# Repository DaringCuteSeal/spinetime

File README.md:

# Spinetime

[Magazine PDF](showcase/zine.pdf)

[Watch the short demo here!](https://www.youtube.com/shorts/rvpcNDkeEeY)

---

Spinetime is a ring binder-integrated _linear clock [^1]_ designed to help
students and neurodivergent individuals manage time and tasks more effectively.
Users of Spinetime can visualize the passage of the day at a glance, providing
aid especially for those who struggle with time blindness.

## Why?

It is surprising to me that people have manufactured papers with time table
template, but not invent something as simple as a pointer that tells you how
far you have gone through your table. I suspect that this is because most
people do not experience time blindness, and having some kind of pointer of the
table isn't really all that useful. This is simply not the case for those with
time blindness: **time doesn't really mean anything if presented in the wrong
way.** I hope that the proof of concept that came with Spinetime may help
present time meaningfully for those who struggle with time blindness like me.

## Background

As someone who suffers from time blindness on a daily basis, I find managing my
time extremely challenging. It's been intensely hard to picture how I'll spend
my time for a particular day. Having shuffled between multiple time management
methods, I constantly find myself at home when I plan my day out on my physical
journal. I simply love the tactile feel of using a physical tool to plan out my
day.

However, being the visual-oriented person I am, lacking any visual cue of
"where" in the time dimension I am at any given day has been a major
deal-breaker that has kept me from using physical tools for journalling. Of
course, journalling papers with pre-made time tables exist, but they don't tell
me what time it really is right now in any tangible manner relating to the table
itself—what a bummer.

I've been using [ChronoCat](https://chronocat.app/) (not affiliated) to manage
my time lately, and it's been a perfect digital tool—minimalistic,
very visual, and easy to use. It provides the user with a
time table alongside a visual cue of where they are within the day.
However, like I said before, I crave the tactile feel of physical
note-taking. It'd also be great if I can plan my day without the distraction
that comes with using a full-fledged mobile phone or computer.
Plus, being able to plan my day at school would be a great[^2]. I always
dream that one day, I won't forget several of my appointments again.

I looked at my own journalling book again, and thought: _you know, I
think that ChronoCat's approach doesn't have to be in the form of a
digital app._ And so, I came up with SpineTime.

## How to Use

**Daily use**: simply strap Spinetime to your ring binder by opening the spine and inserting
the linear clock component and start annotating your day. This repository hosts
the A6 binder-compatible
version.

**How to charge the battery**: charge with a type-C cable. 5V, obviously. The controller implements load sharing so you'll be powering the circuit directly with the given 5V when charged.

## How it Works
The LEDs of the bookmark are controlled by a separate controller unit. An ATtiny1616 MCU is used alongside a DS3231 RTC.

## Specs
- Power usage: about 20-25 mA when bookmark is on (3.7V * 25mA = 92.5 mW). Depends on LED color. 7 mA when bookmark is switched off (3.7V * 7mA = 25.9 mW).
- Use duration: about 1d 16h (1000 mAh ÷ 25 mA). Probably a bit lower since we won't (and can't) use the full capacity of the battery.

## Build Instruction
You will need:
1. A soldering iron
2. Solder
3. Everything from [BOM](#BOM)
4. A USB-to-TTL adapter such as a CH340 breakout module
5. Wire crimper
6. Wire stripper
7. Scissors
8. USB-C cable
9. 3 jumper wires (female-to-female)

Steps:
1. Print the [PCBs](#Project-Design-Showcase). Customize if needed. Note that the gerbers aren't included, so you'd have to generate them first from KiCad.
2. Solder components listed on the [BOM](#BOM) according to the PCB file.
3. 3D print the casing components.
4. Use whatever set of cables you have (can be thin) and solder the bookmark's VIN, GND, and DAT through-holes to the cables. Crimp the end into the 3-pin JST housing. Make sure the orientation is aligned correctly with the controller (as JST connectors cannot be plugged in both orientations).
5. Put together everything into the casing: the battery, the controller PCB, and the anti-slip rubbers (might need to be cut to the correct size first, fitting the casing's square indents).
6. If your battery hasn't been crimped yet, crimp the cables to the 2-pin JST. Then plug the battery connector to the controller.
7. Build the [firmware](#firmware). Customize as you wish. You'll need [PlatformIO](https://platformio.org/).
8. FLash the firmware. Initially, set `SET_TIME` to `true` in the `cfg.h` file first to set time, then flash again with `SET_TIME` set to `false`. You will need a USB-to-TTL adapter. Connect the TX pin of the adapter to the TX pin of SpineTime's controller PCB and the RX pin of the adapter to RX. Note that the PCB doesn't have labels for that.. just check the kicad file to know which is which :P. Then, connect the adapter's ground accordingly.
9. You should be done! There's no screw assembly required—everything uses compliant mechanism.

Gotchas:
1. If you can't flash the ATtiny1616, try changing to another device. Initially I couldn't flash my ATtiny and as it turns out, my laptop has a bad USB controller.
2. Some sources online say that SK6812 LEDs are difficult to solder and require lower temp but I found that with hand-soldering, even up to ~350°C is fine. (just don't roast the LEDs for 1 minute straight I guess)

## Spelling
Spinetime, SpineTime, spinetime are all valid. No spineTime or spine_time or anything else.
## Project Design Showcase

### IRL Build

Note: I built it with LEDs too big so I didn't put on the casing lid.

### PCBs

The actual bookmark ([project files](kicad/bookmark), [.step file](kicad/bookmark/bookmark.step)):

The controller unit ([project files](kicad/controller), [.step file](kicad/controller/controller.step)):

Schematics:

- [Schematic of controller unit](showcase/controller.pdf)
- [Schematic of bookmark unit](showcase/bookmark.pdf)

### 3D Models

The model files can be found under [freecad/](freecad/).

Casing:

Support clip (so your book cover won't wobble when being written on):

### Firmware
The firmware files for SpineTime, `spinetime-fw`, can be [found in the firmware directory](./firmware).

## BOM
[BOM/bill of materials for this project can be found here](bom/bom.csv).

## Credits

Thanks to [Hack Club](https://hackclub.com/) for supporting! Initially made for [Hack Club Blueprint](https://blueprint.hackclub.com), but later got transferred to [Hack Club Fallout](https://fallout.hackclub.com/).

**Awesome software used:**
- [KiCad](https://www.kicad.org/) (as EDA)
- [Blender](https://www.blender.org/) (for designing mockup)
- [FreeCAD](https://www.freecad.org/) (as CAD)
- [NeoVim](https://neovim.io/) (as IDE)
- [VSCode](https://code.visualstudio.com/) (as IDE)
- [PlatformIO](https://platformio.org/) (as embedded programming platform)
- [Kitty](https://sw.kovidgoyal.net/kitty/) (as terminal)
- [Git](https://git-scm.com/) (as SVC)
- [Artix Linux!](https://artixlinux.org)

**Awesome services used:**
- [Github](.) (hosting project files)

**I used several 3D models for my PCB 3D model:**
- https://grabcad.com/library/usb-type-c-smd-6pin-1
- https://grabcad.com/library/2-pins-jst-1
- https://grabcad.com/library/3-pins-jst-1

**References (unfortunately not all, just the very notable ones):**
- megaTinyCore, awesome core + documentations for my ATTiny: https://github.com/SpenceKonde/megaTinyCore)
- Datasheet of all components I used. I'm not sure if I wanna include all of the links back because I didn't keep track of them, but feel free to ask for the documents I have locally directly to maybe figure out the source.
- NeoPixel guide: https://learn.adafruit.com/adafruit-neopixel-uberguide/logic-level
- Another NeoPixel guide: https://www.digikey.com/en/maker/projects/adafruit-neopixel-berguide/970445a726c1438a9023c1e78c42e0bb
- How to flash ATtiny1616: https://michael-crum.com/attiny1616/
- Changing clock speed of ATtiny1616: https://www.avrfreaks.net/s/topic/a5C3l000000Ubn4EAC/t159058
- Technical problems with SK6812: https://forums.adafruit.com/viewtopic.php?t=188940
- Sk6812 is hard to solder?: https://www.makerfabs.com/blog/post/how-makerfabs-solve-the-oled-sticking-problem
- Order with moisture-sensitive devices recommendations: https://jlcpcb.com/help/article/moisture-sensitivity-level-msl-for-electronic-parts
- Load-sharing circuit: https://www.thanassis.space/loadsharing.html
- SMD resistor guide: https://www.allpcb.com/blog/pcb-assembly/smd-resistors-demystified-sizes-markings-and-practical-applications.html
- Should LED strip's end be connected to anything?: https://www.reddit.com/r/AskElectronics/comments/1bnx4vv/addressable_led_data_out_connect_to_ground_yn/
- TP4056 breakout reference: https://github.com/alltheworld/tp4056/issues/3
- Setting internal reference voltage for attiny1616: https://forum.arduino.cc/t/how-to-measure-supply-voltage-in-attiny/1244260

Huh, am I over-crediting? maybe..
## LLM Usage Disclosure
I used [ChatGPT](https://chatgpt.com) for sanity-checking my configurations (including my controller schematic, for instance it caught that I didn't pull the CC pins to ground).

[^1]: Analog clock that shows time in a linear format, instead of the usual
12-hour wrap-around style. This clock is often suggested for those with ADHD &
time blindness.

[^2]: My school does not allow the use of mobile phone/laptop during class and
recess.

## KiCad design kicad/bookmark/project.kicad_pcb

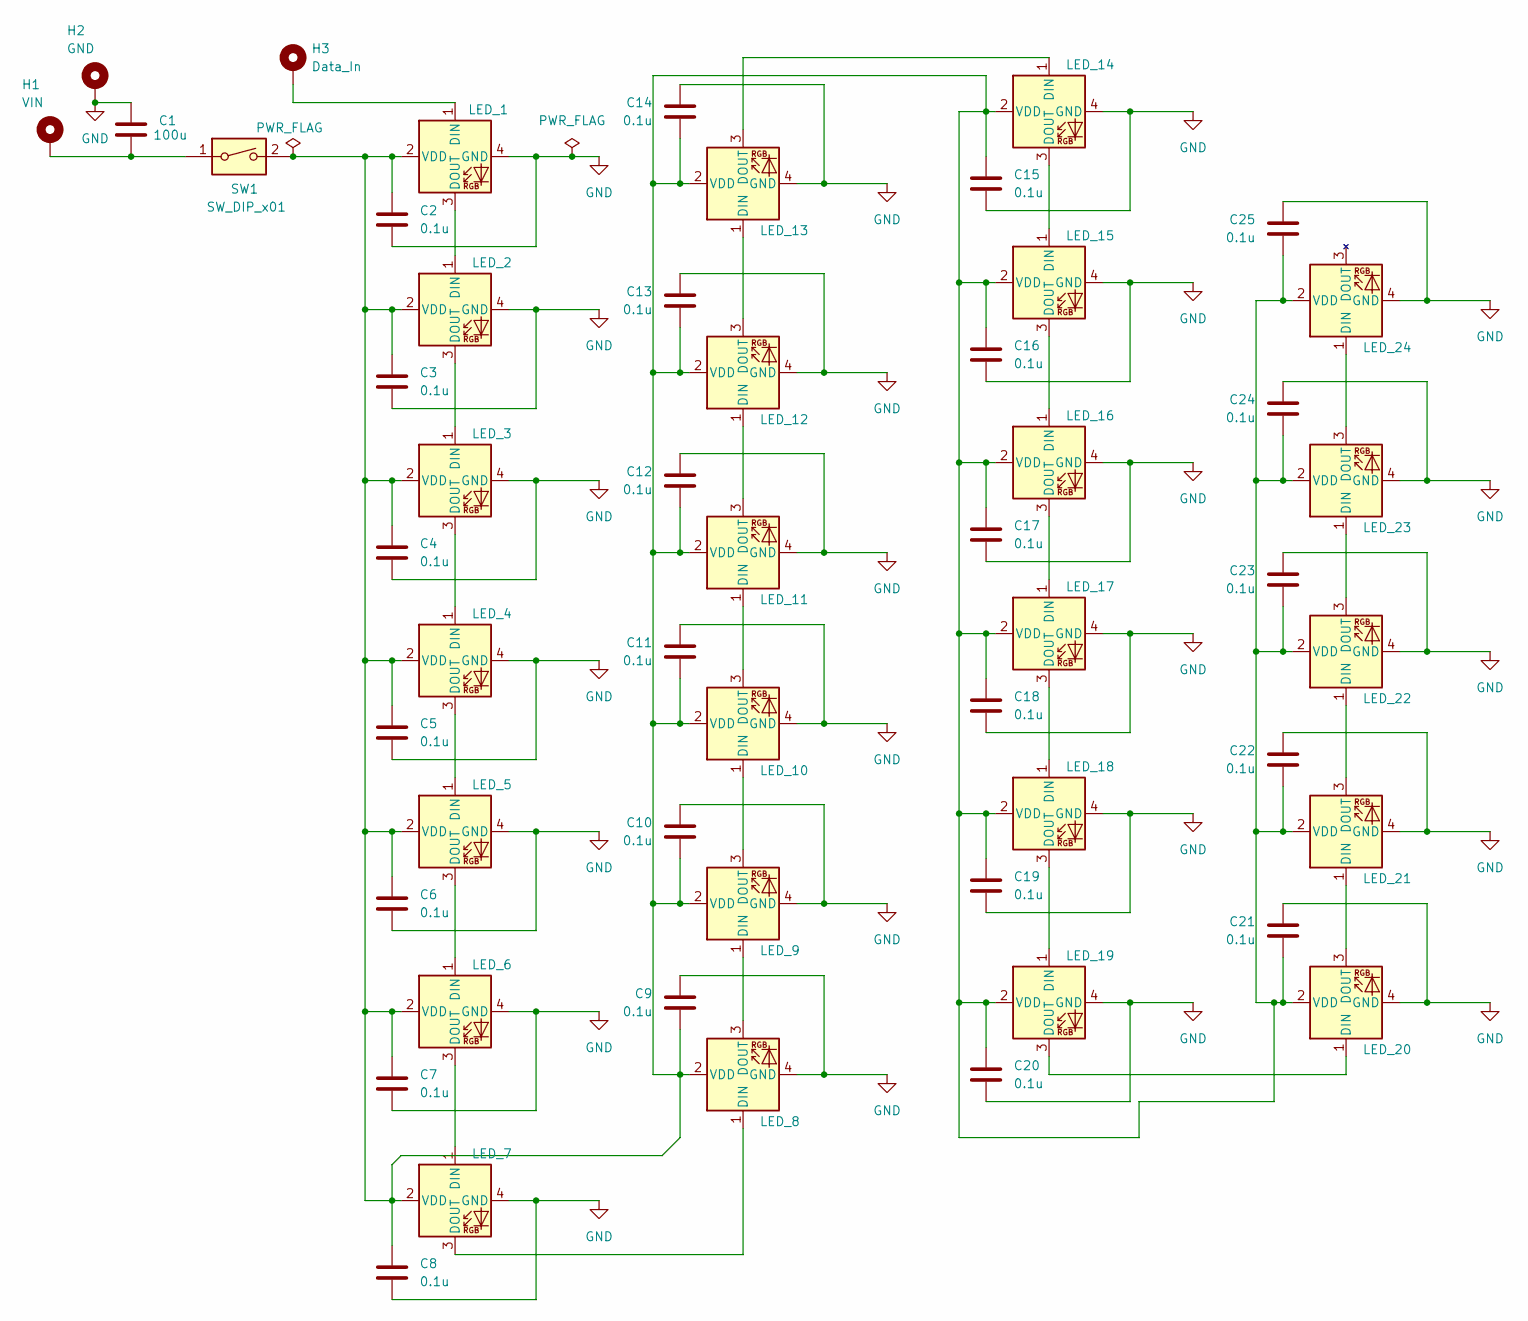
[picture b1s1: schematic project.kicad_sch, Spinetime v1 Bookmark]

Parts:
C1: 100u; C_1206_3216Metric
C2, C3, C4, C5, C6, C7, C8, C9, C10, C11, C12, C13, C14, C15, C16, C17, C18, C19, C20, C21, C22, C23, C24, C25: 0.1u; C_0402_1005Metric
D1: LED_1; LED-SMD_4P-L4.0-W1.6-L
D2: LED_2; LED-SMD_4P-L4.0-W1.6-L
D3: LED_3; LED-SMD_4P-L4.0-W1.6-L
D4: LED_4; LED-SMD_4P-L4.0-W1.6-L
D5: LED_5; LED-SMD_4P-L4.0-W1.6-L
D6: LED_6; LED-SMD_4P-L4.0-W1.6-L
D7: LED_7; LED-SMD_4P-L4.0-W1.6-L
D8: LED_8; LED-SMD_4P-L4.0-W1.6-L
D9: LED_9; LED-SMD_4P-L4.0-W1.6-L
D10: LED_10; LED-SMD_4P-L4.0-W1.6-L
D11: LED_11; LED-SMD_4P-L4.0-W1.6-L
D12: LED_12; LED-SMD_4P-L4.0-W1.6-L
D13: LED_13; LED-SMD_4P-L4.0-W1.6-L
D14: LED_14; LED-SMD_4P-L4.0-W1.6-L
D15: LED_15; LED-SMD_4P-L4.0-W1.6-L
D16: LED_16; LED-SMD_4P-L4.0-W1.6-L
D17: LED_17; LED-SMD_4P-L4.0-W1.6-L
D18: LED_18; LED-SMD_4P-L4.0-W1.6-L
D19: LED_19; LED-SMD_4P-L4.0-W1.6-L
D20: LED_20; LED-SMD_4P-L4.0-W1.6-L
D21: LED_21; LED-SMD_4P-L4.0-W1.6-L
D22: LED_22; LED-SMD_4P-L4.0-W1.6-L
D23: LED_23; LED-SMD_4P-L4.0-W1.6-L
D24: LED_24; LED-SMD_4P-L4.0-W1.6-L
H1: VIN; THT_hole_2mm
H2: GND; THT_hole_2mm
H3: Data_In; THT_hole_2mm
SW1: SW_DIP_x01; SW-SMD_CHS-01B

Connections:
GND: C1.1, C2.2, C3.2, C4.2, C5.2, C6.2, C7.2, C8.2, C9.2, C10.2, C11.2, C12.2, C13.2, C14.2, C15.2, C16.2, C17.2, C18.2, C19.2, C20.2, C21.2, C22.2, C23.2, C24.2, C25.2, D1.4 (GND), D2.4 (GND), D3.4 (GND), D4.4 (GND), D5.4 (GND), D6.4 (GND), D7.4 (GND), D8.4 (GND), D9.4 (GND), D10.4 (GND), D11.4 (GND), D12.4 (GND), D13.4 (GND), D14.4 (GND), D15.4 (GND), D16.4 (GND), D17.4 (GND), D18.4 (GND), D19.4 (GND), D20.4 (GND), D21.4 (GND), D22.4 (GND), D23.4 (GND), D24.4 (GND), H2.1 (1_1)
unnamed: C1.2, H1.1 (1_1), SW1.1
unnamed: D1.1 (DIN), H3.1 (1_1)
unnamed: D1.3 (DOUT), D2.1 (DIN)
unnamed: C2.1, C3.1, C4.1, C5.1, C6.1, C7.1, C8.1, C9.1, C10.1, C11.1, C12.1, C13.1, C14.1, C15.1, C16.1, C17.1, C18.1, C19.1, C20.1, C21.1, C22.1, C23.1, C24.1, C25.1, D1.2 (VDD), D2.2 (VDD), D3.2 (VDD), D4.2 (VDD), D5.2 (VDD), D6.2 (VDD), D7.2 (VDD), D8.2 (VDD), D9.2 (VDD), D10.2 (VDD), D11.2 (VDD), D12.2 (VDD), D13.2 (VDD), D14.2 (VDD), D15.2 (VDD), D16.2 (VDD), D17.2 (VDD), D18.2 (VDD), D19.2 (VDD), D20.2 (VDD), D21.2 (VDD), D22.2 (VDD), D23.2 (VDD), D24.2 (VDD), SW1.2
unnamed: D2.3 (DOUT), D3.1 (DIN)
unnamed: D3.3 (DOUT), D4.1 (DIN)
unnamed: D4.3 (DOUT), D5.1 (DIN)
unnamed: D5.3 (DOUT), D6.1 (DIN)
unnamed: D6.3 (DOUT), D7.1 (DIN)
unnamed: D7.3 (DOUT), D8.1 (DIN)
unnamed: D8.3 (DOUT), D9.1 (DIN)
unnamed: D9.3 (DOUT), D10.1 (DIN)
unnamed: D10.3 (DOUT), D11.1 (DIN)
unnamed: D11.3 (DOUT), D12.1 (DIN)
unnamed: D12.3 (DOUT), D13.1 (DIN)
unnamed: D13.3 (DOUT), D14.1 (DIN)
unnamed: D14.3 (DOUT), D15.1 (DIN)
unnamed: D15.3 (DOUT), D16.1 (DIN)
unnamed: D16.3 (DOUT), D17.1 (DIN)
unnamed: D17.3 (DOUT), D18.1 (DIN)
unnamed: D18.3 (DOUT), D19.1 (DIN)
unnamed: D19.3 (DOUT), D20.1 (DIN)
unnamed: D20.3 (DOUT), D21.1 (DIN)
unnamed: D21.3 (DOUT), D22.1 (DIN)
unnamed: D22.3 (DOUT), D23.1 (DIN)
unnamed: D23.3 (DOUT), D24.1 (DIN)

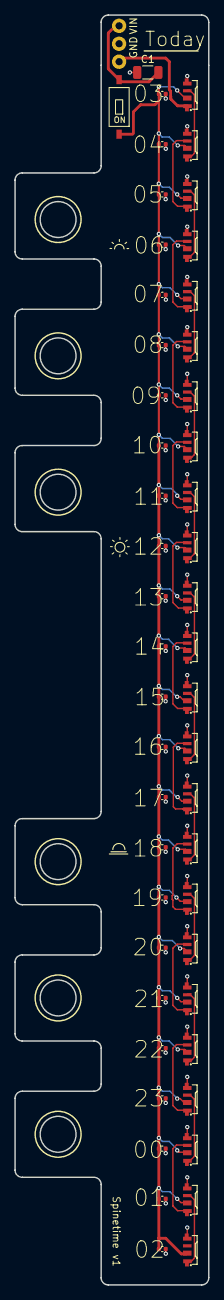
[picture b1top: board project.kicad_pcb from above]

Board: 2 copper layers, 27.0 x 177.0 mm, 53 parts (0 on the bottom side), 27 nets.

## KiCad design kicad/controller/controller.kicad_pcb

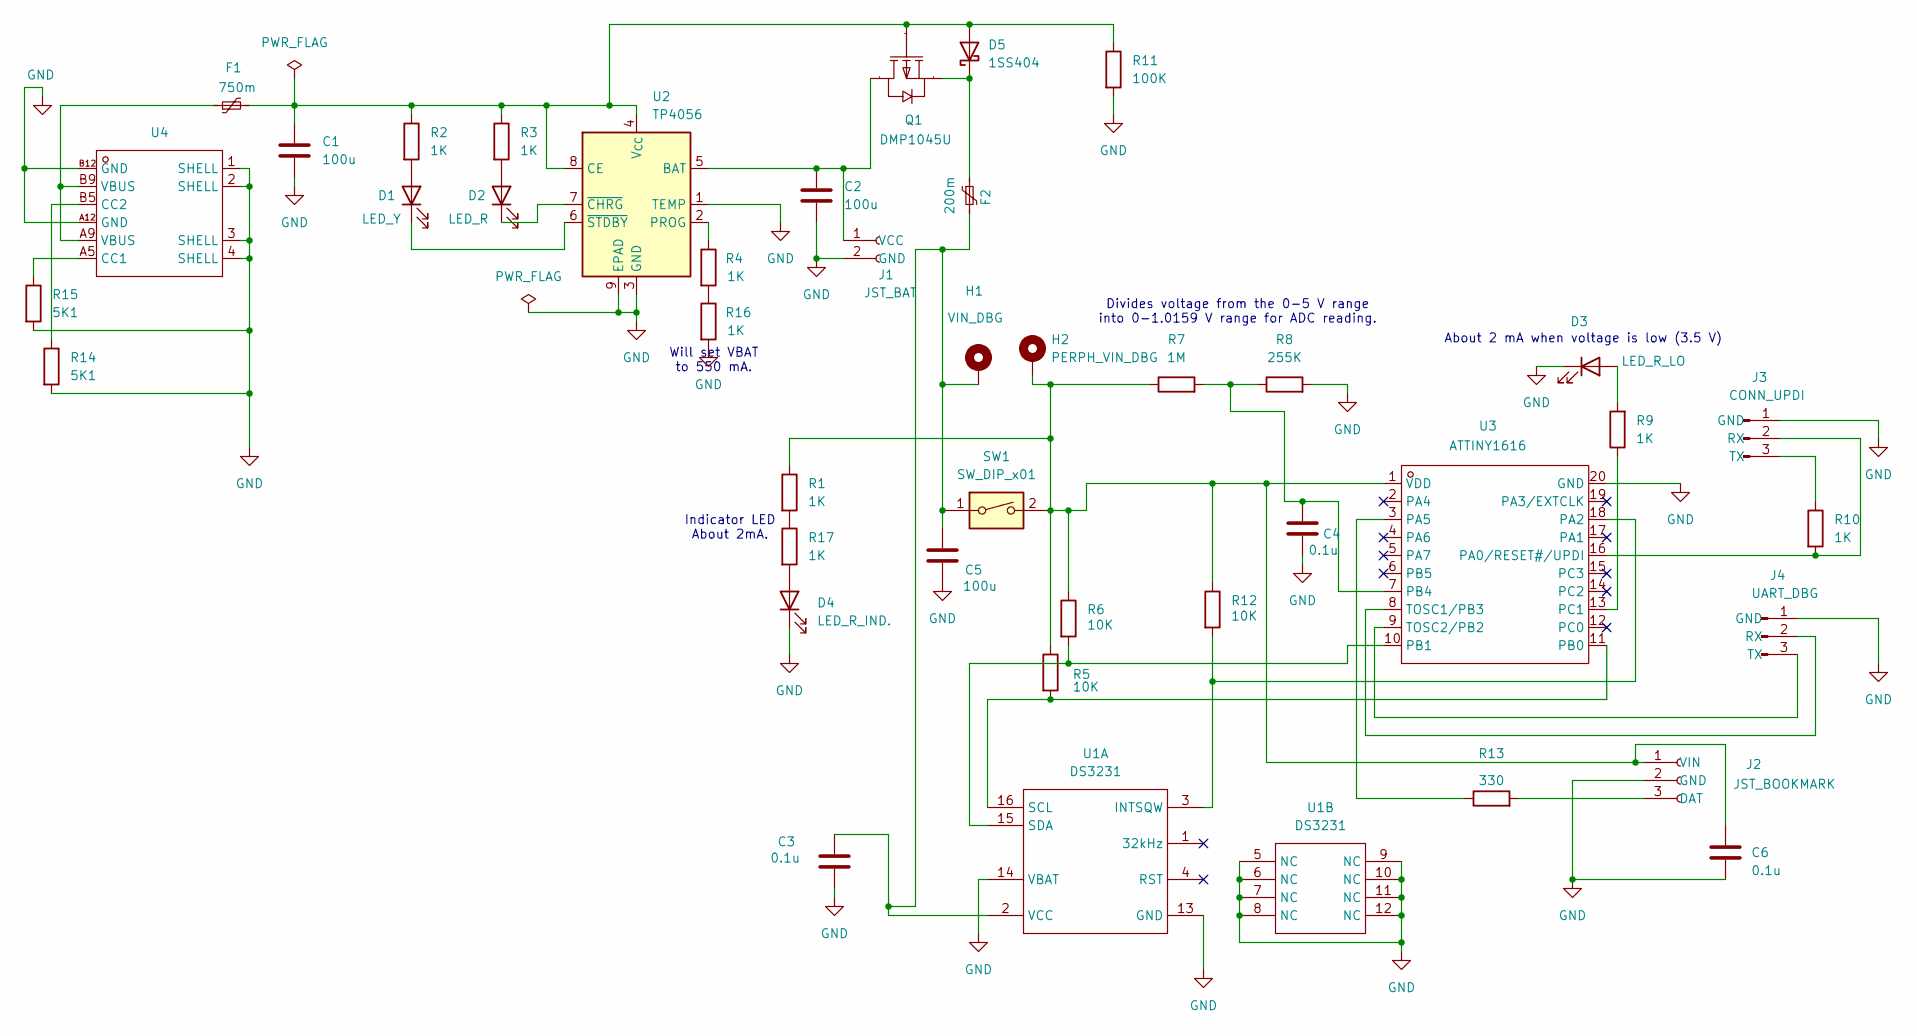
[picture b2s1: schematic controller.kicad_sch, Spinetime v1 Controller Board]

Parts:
C1, C2, C5: 100u; C_1206_3216Metric
C3, C4, C6: 0.1u; C_0402_1005Metric
D1: LED_Y; LED_D2.0mm_W4.8mm_H2.5mm_FlatTop
D2: LED_R; LED_D2.0mm_W4.8mm_H2.5mm_FlatTop
D3: LED_R_LO; LED_D2.0mm_W4.8mm_H2.5mm_FlatTop
D4: LED_R_IND.; LED_D2.0mm_W4.8mm_H2.5mm_FlatTop
D5: 1SS404; D_SOD-323
F1: 750m; Fuse_1812_4532Metric
F2: 200m; Fuse_1812_4532Metric
H1: VIN_DBG; SolderWirePad_1x01_SMD_1x2mm
H2: PERPH_VIN_DBG; SolderWirePad_1x01_SMD_1x2mm
J1: JST_BAT; JST_1x2_2.54mm-horizontal_1
J2: JST_BOOKMARK; JST_1x3_2.54mm-horizontal
J3: CONN_UPDI; PinHeader_1x03_P2.54mm_Vertical
J4: UART_DBG; PinHeader_1x03_P2.54mm_Vertical
Q1: DMP1045U; SOT-23-3_L2.9-W1.5-P1.90-LS2.6-BR; Manufacturer Part DMP1045U-HXY; LCSC Part Name 1个P沟道 耐压:20V 电流:5A
R1, R2, R3, R4, R9, R10, R16, R17: 1K; R_0603_1608Metric
R5, R6, R12: 10K; R_0603_1608Metric
R7: 1M; R_0603_1608Metric
R8: 255K; R_0603_1608Metric
R11: 100K; R_0603_1608Metric
R13: 330; R_0603_1608Metric
R14, R15: 5K1; R_0603_1608Metric
SW1: SW_DIP_x01; SW-SMD_CHS-01B
U1: DS3231; SOIC-16_L10.3-W7.5-P1.27-LS10.3-BL; Manufacturer Part DS3231SN#T&R; LCSC Part Name 超高精度、I²C接口、集成RTC/TCXO/晶体
U2: TP4056; SOIC-8-1EP_3.9x4.9mm_P1.27mm_EP2.41x3.3mm_ThermalVias
U3: ATTINY1616; SOIC-20_L12.8-W7.5-P1.27-LS10.3-BL; Manufacturer Part ATTINY1616-SNR; LCSC Part Name tinyAVR 1系列微控制器
U4: USB-C-SMD_USB-TYPE-C-006; Manufacturer Part USB-TYPE-C-006; LCSC Part Name Type-C 母 卧贴

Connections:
GND: C1.2, C2.2, C3.2, C4.2, C5.2, C6.2, D3.1 (K), D4.1 (K), J1.2 (GND), J2.2 (GND), J3.1 (GND), J4.1 (GND), R8.2, R11.2, R14.2, R15.2, R16.2, U1.5 (NC), U1.6 (NC), U1.7 (NC), U1.8 (NC), U1.9 (NC), U1.10 (NC), U1.11 (NC), U1.12 (NC), U1.13 (GND), U1.14 (VBAT), U2.1 (TEMP), U2.3 (GND), U2.9 (EPAD), U3.20 (GND), U4.1 (SHELL), U4.2 (SHELL), U4.3 (SHELL), U4.4 (SHELL), U4.A12 (GND), U4.B12 (GND)
unnamed: D1.2 (A), R2.2
unnamed: D1.1 (K), U2.6 (~STDBY)
unnamed: D2.2 (A), R3.2
unnamed: D2.1 (K), U2.7 (~CHRG)
unnamed: D3.2 (A), R9.2
unnamed: D4.2 (A), R17.2
unnamed: C1.1, D5.2 (A), F1.2, Q1.1 (G), R2.1, R3.1, R11.1, U2.4 (V_{CC}), U2.8 (CE)
unnamed: D5.1 (K), F2.1, Q1.2 (S)
unnamed: F1.1, U4.A9 (VBUS), U4.B9 (VBUS)
unnamed: C2.1, J1.1 (VCC), Q1.3 (D), U2.5 (BAT)
unnamed: J2.3 (DAT), R13.2
unnamed: C6.1, H2.1 (1_1), J2.1 (VIN), R1.1, R5.1, R6.1, R7.1, R12.1, SW1.2, U3.1 (VDD)
unnamed: J3.2 (RX), R10.2, U3.16 (PA0/RESET#/UPDI)
unnamed: J3.3 (TX), R10.1
unnamed: J4.2 (RX), U3.8 (TOSC1/PB3)
unnamed: J4.3 (TX), U3.9 (TOSC2/PB2)
unnamed: R1.2, R17.1
unnamed: R4.2, R16.1
unnamed: R12.2, U1.3 (INTSQW), U3.18 (PA2)
unnamed: R5.2, U1.16 (SCL), U3.11 (PB0)
unnamed: R6.2, U1.15 (SDA), U3.10 (PB1)
unnamed: C3.1, C5.1, F2.2, H1.1 (1_1), SW1.1, U1.2 (VCC)
unnamed: R4.1, U2.2 (PROG)
unnamed: R13.1, U3.3 (PA5)
unnamed: C4.1, R7.2, R8.1, U3.7 (PB4)
unnamed: R9.1, U3.13 (PC1)
unnamed: R15.1, U4.A5 (CC1)
unnamed: R14.1, U4.B5 (CC2)

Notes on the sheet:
Indicator LED About 2mA.
Divides voltage from the 0-5 V range into 0-1.0159 V range for ADC reading.
Will set VBAT to 550 mA.
About 2 mA when voltage is low (3.5 V)

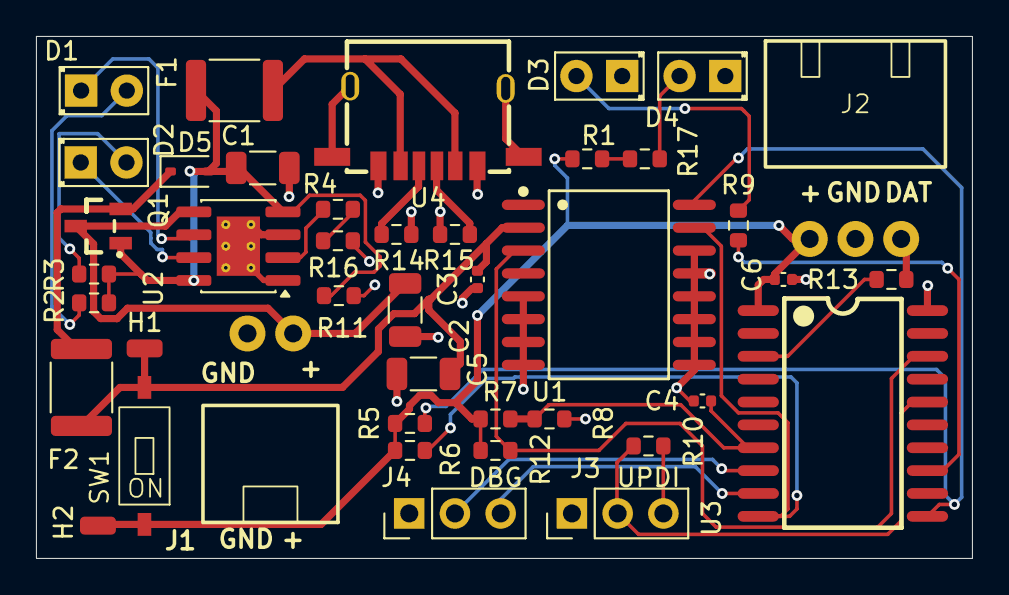
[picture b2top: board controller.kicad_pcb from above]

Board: 2 copper layers, 52.0 x 29.0 mm, 42 parts (0 on the bottom side), 29 nets.

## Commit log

2026-02-15 docs: add README file
2026-02-15 docs: improve README file formatting & grammar
2026-02-15 docs: remove use of pascalcase project name
2026-03-26 add project and model files
2026-03-28 fix: correct LED footprints
2026-03-28 fix: fix wrong UPDI & DBG pin label
2026-03-29 chore: rename model/ to mockup/
2026-03-29 fix: make sense of the connection from power to peripherals make the DS3231 get power directly without a switch and add testing pads to connect power to MCU & LEDs in order to measure current.
2026-03-29 revert 6c72ed
2026-03-29 clean up position of footprints
2026-03-29 do not track backup files
2026-03-29 timespine? wut lol bro
2026-03-29 add mockup image and blend file
2026-03-29 do not track unimportant kicad project files
2026-03-29 add showcase files
2026-03-29 ignore lock files
2026-03-29 add freecad models
2026-03-29 add assets to readme.md
2026-03-29 add pcb .step files
2026-05-09 change usb C footprint to USB-TYPE-C-006 https://jlcpcb.com/partdetail/DEALON-USB_TYPE_C006/C2927026
2026-05-10 fix(controller): change output directory
2026-05-10 remove drill files
2026-05-10 edit gitignore
2026-05-10 fix(bookmark): change 22uF value to 100uF cheapo. controller only uses 100uF and 0.1uF
2026-05-11 add BOM
2026-05-11 bom: add anti-slip rubber
2026-05-15 add zine
2026-05-15 add BOM link
2026-05-15 fix(readme): fix weird wording about time blindness
2026-05-15 fix(readme): add fallout status
2026-05-15 fix(bom): add awg28 cable
2026-05-15 fix(bom): add "1 set" to jst
2026-05-15 fix(readme): add more elaborate usage and build guide
2026-05-15 fix(readme): add gerbers disclaimer
2026-05-15 fix(zine): fix misaligned magic light
2026-05-15 fix(readme): fix order of build instruction and add instruction to set time
2026-05-15 add firmware to here..
2026-06-10 fix typo
2026-06-10 fix updi pins
2026-06-11 fix(firmware): fix order of function definition
2026-06-11 fix(firmware): fix pin used for battery voltage
2026-06-11 fix(platformio.ini): set serial_updi to serialupdi protocol
2026-06-11 fix(firmware): use digitalWrite instead of whatever digitalWriteFast is
2026-06-11 add default upload baud rate
2026-06-11 add gitignore file for firmware folder
2026-06-11 add platformio extension recommendation for firmware
2026-06-11 feat(firmware): use idle mode for sleep so i dont get locked out of programming
2026-06-11 fix(firmware): set sleep mode to idle
    to prevent getting locked up..
2026-06-11 feat(firmware): add LED status before executing routine
2026-06-11 docs(firmware): fix system_power_down comment
2026-06-12 fix function signature for modulo function
2026-06-12 firmware: set new correct low battery thresh for the new voltage divider
2026-06-12 fix(firmware): correct the code to select vref
2026-06-12 fix(firmware): fix time setting function
2026-06-12 firmware: literally no sleep so i dont lock myself out of updi lol
2026-06-12 firmware: remove interrupt pin definition
2026-06-12 firmware: add voltage divider notice
2026-06-12 firmware: add back battery low indicator no async running cuz im lazy this is just so i dont forget
2026-06-14 fix(firmware): fix LED not showing up
2026-06-14 fix(firmware): light blend logic
2026-06-15 feat(firmware): flash LED strip too when low battery
2026-06-15 fix(firmware): better doc for LOW_BAT_THRESH and set to 600
2026-06-15 docs(firmware): remove bloated LED docs on cfg.h
2026-06-15 docs(firmware): change default color to good amber
2026-06-15 update prices getting more expensive smh
2026-06-15 replace out of stock resistors with fresh ones * swap 1M+255K voltage divider to 787K+200K * swap 330 to 330 but less power rating the entire bom is now $0.1 cheaper!
2026-06-15 change shipping method, remove hard-to-predict prices tax price calculation will go stale after i receive them anyway smh
2026-06-15 fix zine image?
2026-06-15 update zines
2026-06-15 add link to demo
2026-06-15 add build note
2026-06-15 add irl pics
2026-06-15 add power usage
2026-06-15 remove useless files
2026-06-15 remove weird bookmark.bin file
